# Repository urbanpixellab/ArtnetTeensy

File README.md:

# ArtnetTeensy

# Artnet receiver issues by now

testsetup: sending 8 universes all doing the same, turning on one led per frame -> after 150 leds on it restarts.

network issues: 
Wifi: ping ~ 2-4ms , led animation is stotering but all are working
Cabled network: ping ~0.3ms, led animation are not visible, serial print shows only 0-2 universes are received on the teensy

# edit the right etherneth library, i change dthe teensy ethernet library not the arduino

* change the ws5200 size to 8kb incl the mask and change the sockets to one
* and overclock the 3.2 to 96mhz

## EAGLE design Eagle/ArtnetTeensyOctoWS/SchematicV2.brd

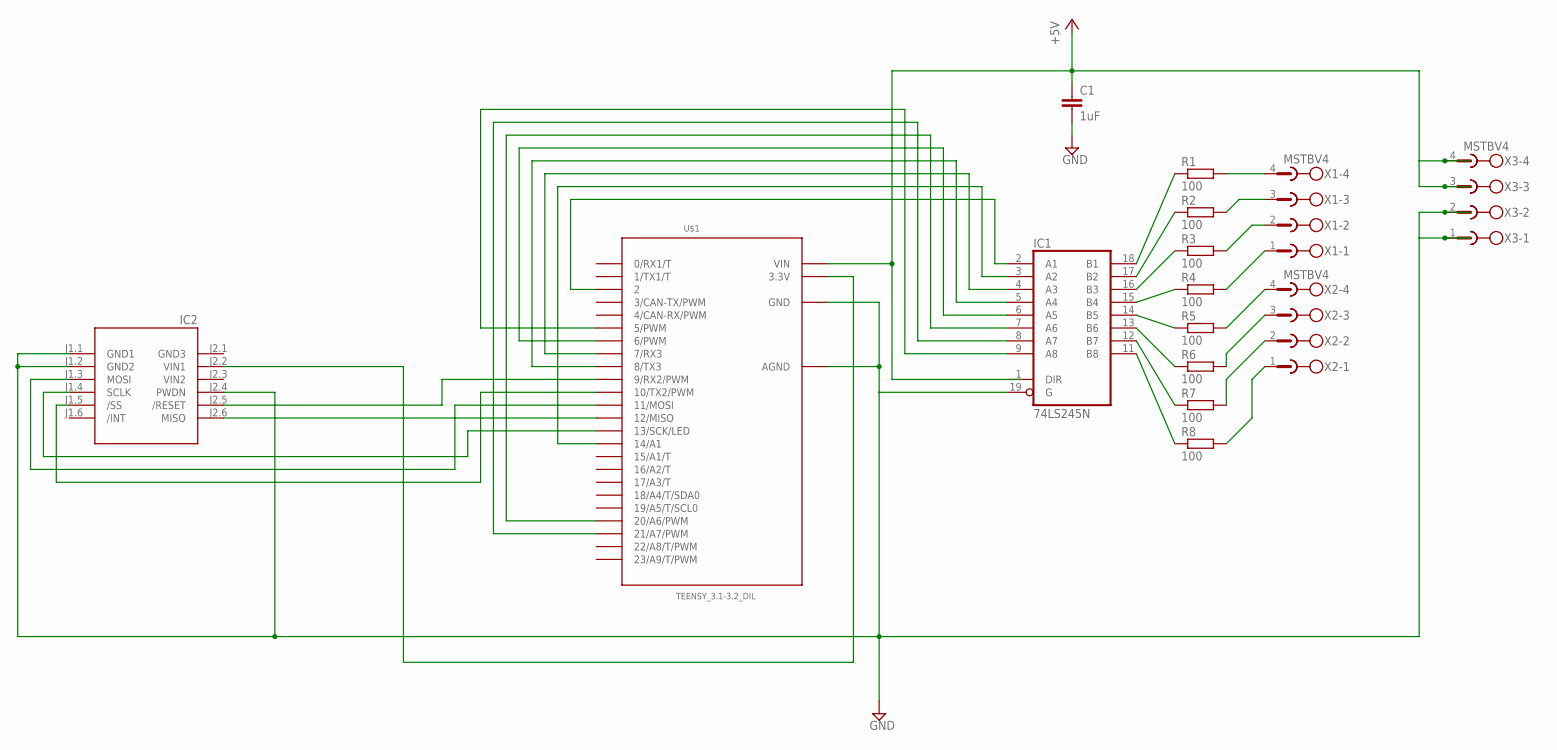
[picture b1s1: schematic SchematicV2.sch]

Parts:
C1: 1uF; C050-035X075
IC1: 74LS245N; DIL20
IC2: WIZ820IO_DEVICE'DUAL-IN-LINE'; WIZ820IO
R1, R2, R3, R4, R5, R6, R7, R8: 100; 0207/7
U$1: TEENSY_3.1-3.2_DIL; TEENSY_3.0-3.2&LC_DIL
X1, X2, X3: MSTBV4

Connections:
+5V: C1.1, U$1.VIN, X3.3, X3.4
GND: C1.2, IC1.10 (GND), IC1.19 (G), IC2.J1.1 (GND1), IC2.J1.2 (GND2), IC2.J2.4 (PWDN), U$1.AGND, U$1.GND, X3.1, X3.2
GND3: IC2.J2.1 (GND3)
unnamed: IC1.18 (B1), R1.1
unnamed: IC1.17 (B2), R2.1
unnamed: IC1.16 (B3), R3.1
unnamed: IC1.15 (B4), R4.1
unnamed: IC1.14 (B5), R5.1
unnamed: IC1.13 (B6), R6.1
unnamed: IC1.12 (B7), R7.1
unnamed: IC1.11 (B8), R8.1
unnamed: IC1.2 (A1), U$1.2
unnamed: IC1.3 (A2), U$1.14/A0 (14/A1)
unnamed: IC1.4 (A3), U$1.7 (7/RX3)
unnamed: IC1.5 (A4), U$1.8 (8/TX3)
unnamed: IC1.6 (A5), U$1.6 (6/PWM)
unnamed: IC1.7 (A6), U$1.20/A6 (20/A6/PWM)
unnamed: IC1.8 (A7), U$1.21/A7 (21/A7/PWM)
unnamed: IC1.9 (A8), U$1.5 (5/PWM)
unnamed: IC2.J2.2 (VIN1), U$1.3.3V
unnamed: IC2.J2.5 (/RESET), U$1.9 (9/RX2/PWM)
unnamed: IC2.J2.6 (MISO), U$1.12 (12/MISO)
unnamed: IC2.J1.3 (MOSI), U$1.11 (11/MOSI)
unnamed: IC2.J1.4 (SCLK), U$1.13 (13/SCK/LED)
unnamed: IC2.J1.5 (/SS), U$1.10 (10/TX2/PWM)
unnamed: R1.2, X1.4
unnamed: R2.2, X1.3
unnamed: R3.2, X1.2
unnamed: R4.2, X1.1
unnamed: R5.2, X2.4
unnamed: R6.2, X2.3
unnamed: R7.2, X2.2
unnamed: R8.2, X2.1
VCC: IC1.20 (VCC)
VIN2: IC2.J2.3 (VIN2)

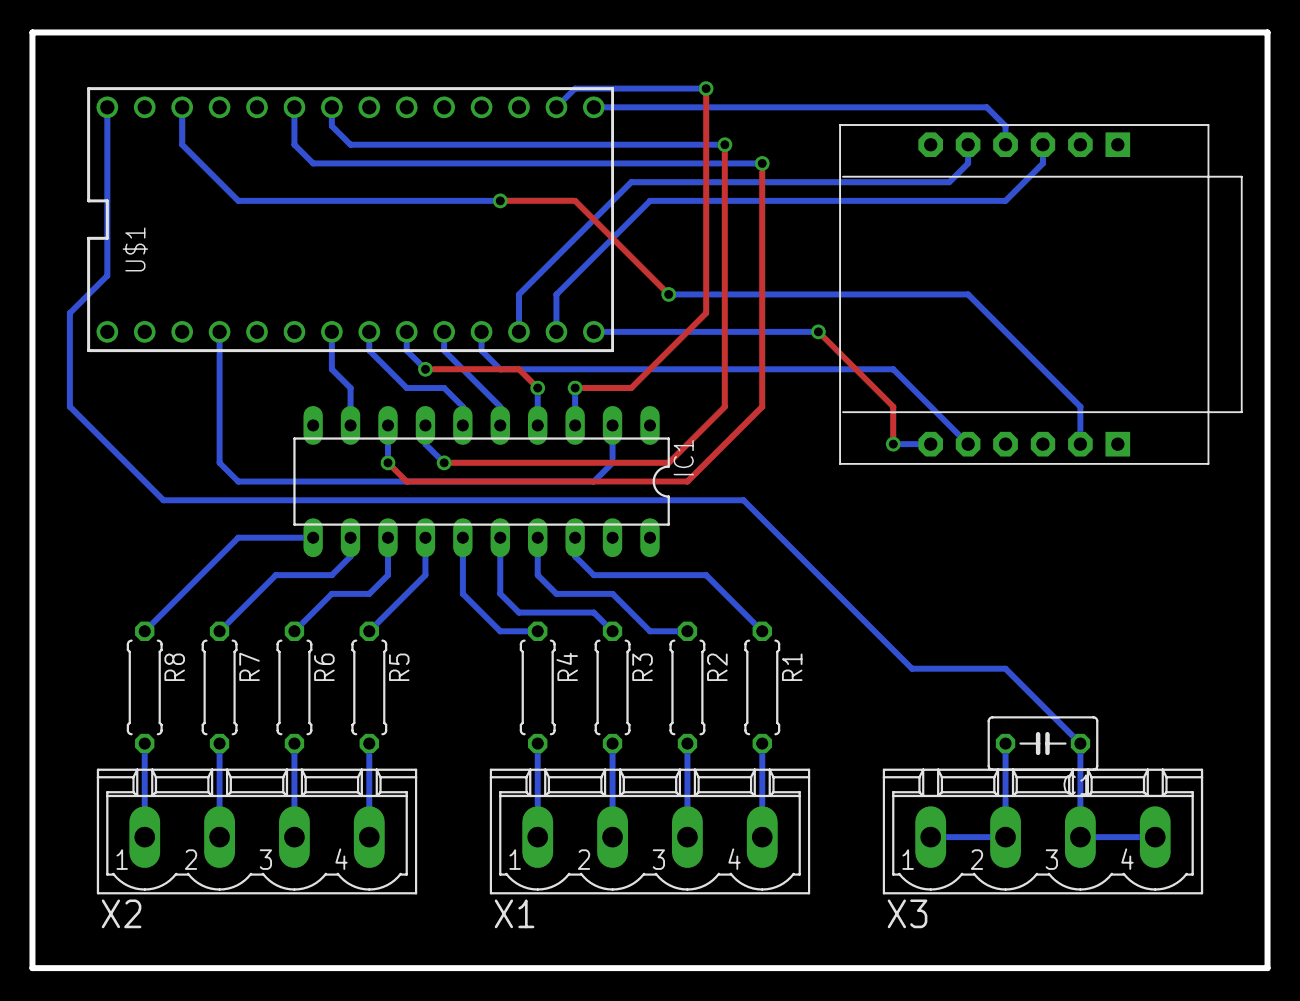
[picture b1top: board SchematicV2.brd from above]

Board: 2 copper layers, 83.8 x 63.5 mm, 15 parts (0 on the bottom side), 32 nets.

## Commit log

2019-03-03 added eagle files
